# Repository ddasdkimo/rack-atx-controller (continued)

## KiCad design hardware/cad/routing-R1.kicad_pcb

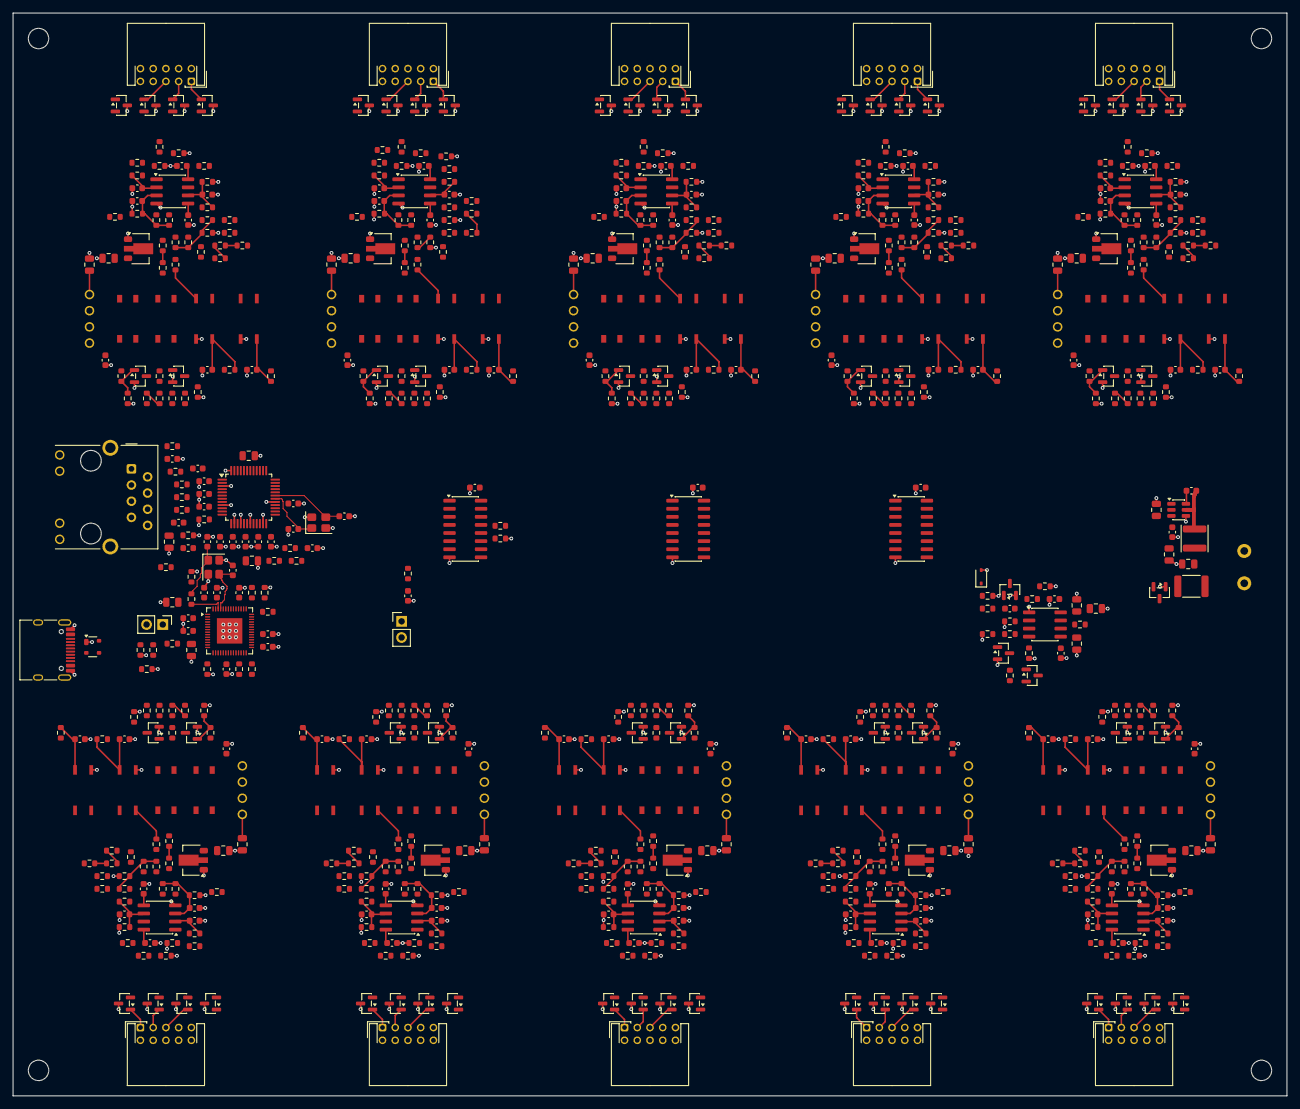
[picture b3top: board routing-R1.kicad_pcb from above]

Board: 2 copper layers, 200.0 x 170.0 mm, 698 parts (0 on the bottom side), 455 nets.

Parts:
C1, C14, C15, C27, C29, C43, C44, C45, C47, C48, C57, C58, C67, C68, C77, C78, C87, C88, C97, C98, C107, C108, C117, C118, C127, C128, C137, C138: 10u; C_0805_2012Metric
C2, C3, C6, C8, C9, C10, C11, C12, C13, C21, C22, C23, C24, C25, C26, C28, C37, C38, C39, C40, C42, C49, C59, C69, C79, C89, C99, C109, C119, C129, C139: 100n; C_0603_1608Metric
C4, C5: 22u; C_0805_2012Metric
C7, C16, C30: 1u; C_0603_1608Metric
C17, C18, C31, C32: 20p; C_0603_1608Metric
C19, C46, C56, C66, C76, C86, C96, C106, C116, C126, C136: 4.7u; C_0603_1608Metric
C20, C33, C41: 10n; C_0603_1608Metric
C34, C35: 6.8n; C_0603_1608Metric
C36: 22n; C_0805_2012Metric
C50, C51, C52, C53, C54, C55, C60, C61, C62, C63, C64, C65, C70, C71, C72, C73, C74, C75, C80, C81, C82, C83, C84, C85, C90, C91, C92, C93, C94, C95, C100, C101, C102, C103, C104, C105, C110, C111, C112, C113, C114, C115, C120, C121, C122, C123, C124, C125, C130, C131, C132, C133, C134, C135, C140, C141, C142, C143, C144, C145: 1n; C_0603_1608Metric
D1: PRTR5V0U2X,215; SOT-143
D2: 1N4148WS; D_SOD-323
D3, D4, D5, D6, D7, D8, D9, D10, D11, D12, D13, D14, D15, D16, D17, D18, D19, D20, D21, D22, D23, D24, D25, D26, D27, D28, D29, D30, D31, D32, D33, D34, D35, D36, D37, D38, D39, D40, D41, D42: PESD5V0S2BT; SOT-23
F1: MF-MSMF150/24X-2 1.5A; Fuse_1812_4532Metric
J01, J02, J03, J04, J05, J06, J07, J08, J09, J10: S10B-PHDSS(LF)(SN); JST_PHD_S10B-PHDSS_2x05_P2.00mm_Horizontal
J101: WJ500V-5.08-2P; WJ500V_5.08_2P
J102, J103: PZ254V-11-02P; PinHeader_1x02_P2.54mm_Vertical
J104: TYPE-C-31-M-12; USB_C_Receptacle_HRO_TYPE-C-31-M-12
J105: HR911105A; RJ45_Hanrun_HR911105A_Horizontal
L1: 4.7uH FNR4018S4R7MT; L_Changjiang_FNR4018S
L2: 120R@100MHz GZ1608D121TF; L_0603_1608Metric
MH1, MH2, MH3, MH4: MountingHole_3.2mm_M3
Q1, Q4: AO3401A; SOT-23
Q2, Q3, Q5, Q6, Q7, Q8, Q9, Q10, Q11, Q12, Q13, Q14, Q15, Q16, Q17, Q18, Q19, Q20, Q21, Q22, Q23, Q24: MMBT3904; SOT-23
R1, R2, R3, R4, R15, R16, R17, R25, R29, R30, R31, R33, R35, R36, R37, R47, R49, R55, R58, R60, R62, R68, R71, R72, R82, R84, R90, R93, R95, R97, R103, R106, R107, R117, R119, R125, R128, R130, R132, R138, R141, R142, R152, R154, R160, R163, R165, R167, R173, R176, R177, R187, R189, R195, R198, R200, R202, R208, R211, R212, R222, R224, R230, R233, R235, R237, R243, R246, R247, R257, R259, R265, R268, R270, R272, R278, R281, R282, R292, R294, R300, R303, R305, R307, R313, R316, R317, R327, R329, R335, R338, R340, R342, R348, R351, R352, R362, R364, R370, R373, R375, R377, R383, R386: 10k 1%; R_0603_1608Metric
R5, R24: 0 1%; R_0603_1608Metric
R6, R7: 47 1%; R_0603_1608Metric
R8, R9: 5.1k 1%; R_0603_1608Metric
R10, R11: 33 1%; R_0603_1608Metric
R12, R13, R26, R27, R28, R34, R39, R43, R46, R48, R59, R61, R74, R78, R81, R83, R94, R96, R109, R113, R116, R118, R129, R131, R144, R148, R151, R153, R164, R166, R179, R183, R186, R188, R199, R201, R214, R218, R221, R223, R234, R236, R249, R253, R256, R258, R269, R271, R284, R288, R291, R293, R304, R306, R319, R323, R326, R328, R339, R341, R354, R358, R361, R363, R374, R376: 100k 1%; R_0603_1608Metric
R14: 12.4k 1%; R_0603_1608Metric
R18, R19, R20, R21: 49.9 1%; R_0603_1608Metric
R22, R23, R56, R57, R69, R70, R91, R92, R104, R105, R126, R127, R139, R140, R161, R162, R174, R175, R196, R197, R209, R210, R231, R232, R244, R245, R266, R267, R279, R280, R301, R302, R314, R315, R336, R337, R349, R350, R371, R372, R384, R385: 330 1%; R_0603_1608Metric
R32, R51, R52, R53, R54, R64, R65, R66, R67, R86, R87, R88, R89, R99, R100, R101, R102, R121, R122, R123, R124, R134, R135, R136, R137, R156, R157, R158, R159, R169, R170, R171, R172, R191, R192, R193, R194, R204, R205, R206, R207, R226, R227, R228, R229, R239, R240, R241, R242, R261, R262, R263, R264, R274, R275, R276, R277, R296, R297, R298, R299, R309, R310, R311, R312, R331, R332, R333, R334, R344, R345, R346, R347, R366, R367, R368, R369, R379, R380, R381, R382: 510k 1%; R_0603_1608Metric
R38, R42, R73, R77, R108, R112, R143, R147, R178, R182, R213, R217, R248, R252, R283, R287, R318, R322, R353, R357: 1.5k 1%; R_0603_1608Metric
R40, R41, R44, R45, R75, R76, R79, R80, R110, R111, R114, R115, R145, R146, R149, R150, R180, R181, R184, R185, R215, R216, R219, R220, R250, R251, R254, R255, R285, R286, R289, R290, R320, R321, R324, R325, R355, R356, R359, R360: 220 1%; R_0603_1608Metric
R50, R63, R85, R98, R120, R133, R155, R168, R190, R203, R225, R238, R260, R273, R295, R308, R330, R343, R365, R378: 390k 1%; R_0603_1608Metric
U1: AP63203WU-7; TSOT-23-6
U2: ESP32-S3FN8; QFN-56-1EP_7x7mm_P0.4mm_EP4x4mm
U3: W5500; LQFP-48_7x7mm_P0.5mm
U4, U5, U6: 74HC595D,118; SOIC-16_3.9x9.9mm_P1.27mm
U7: TLC555CDR; SOIC-8_3.9x4.9mm_P1.27mm
U8, U15, U22, U29, U36, U43, U50, U57, U64, U71: B0505S-1WR3L; HENIPER_B0505S_1WR3L
U9, U16, U23, U30, U37, U44, U51, U58, U65, U72: HT7533-1; SOT-89-3
U10, U11, U17, U18, U24, U25, U31, U32, U38, U39, U45, U46, U52, U53, U59, U60, U66, U67, U73, U74: TLP3122A(TPL,E; TLP3122A_11-4M1S
U12, U13, U19, U20, U26, U27, U33, U34, U40, U41, U47, U48, U54, U55, U61, U62, U68, U69, U75, U76: EL357N(B)(TA)-G; EL357N_SOP4
U14, U21, U28, U35, U42, U49, U56, U63, U70, U77: LM393DR; SOIC-8_3.9x4.9mm_P1.27mm
Y1: 40MHz CL12pF; Crystal_SMD_3225-4Pin_3.2x2.5mm
Y2: 25MHz CL12pF; Crystal_SMD_3225-4Pin_3.2x2.5mm

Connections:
3V3: C4.1, C5.1, C8.1, C9.1, C10.1, C11.1, C12.1, C13.1, C14.1, C15.1, C28.1, C29.1, C37.1, C38.1, C39.1, L1.2, L2.1, R1.1, R2.1, R15.1, R16.1, R17.1, R22.1, R23.1, R25.1, R58.1, R71.1, R93.1, R106.1, R128.1, R141.1, R163.1, R176.1, R198.1, R211.1, R233.1, R246.1, R268.1, R281.1, R303.1, R316.1, R338.1, R351.1, R373.1, R386.1, U1.1, U2.2, U2.3, U2.20, U2.46, U2.55, U2.56, U3.28, U3.43, U3.44, U3.45, U4.16, U5.16, U6.16
3V3_ETH_A: C21.1, C22.1, C23.1, C24.1, C25.1, C26.1, C27.1, L2.2, R18.2, R19.2, U3.4, U3.8, U3.11, U3.15, U3.17, U3.21
5V: C1.1, C2.1, C42.1, C46.1, C56.1, C66.1, C76.1, C86.1, C96.1, C106.1, C116.1, C126.1, C136.1, Q1.2, Q4.2, R31.1, R32.1, R35.2, U1.2, U1.3, U7.8, U8.2, U15.2, U22.2, U29.2, U36.2, U43.2, U50.2, U57.2, U64.2, U71.2
5V_FUSED: F1.2, Q1.3
5V_JACK: F1.1, J101.1
BOOT_N: J103.1, R2.2, U2.5
BUCK_BST: C3.1, U1.6
BUCK_SW: C3.2, L1.1, U1.5
CHASSIS: J105.SH, R24.1
CTRL_H01_PWR_A: R41.2, U10.1
CTRL_H01_PWR_B: Q5.1, R38.2, R39.1
CTRL_H01_PWR_K: Q5.3, U10.3
CTRL_H01_PWR_R: R40.2, R41.1
CTRL_H01_RST_A: R45.2, U11.1
CTRL_H01_RST_B: Q6.1, R42.2, R43.1
CTRL_H01_RST_K: Q6.3, U11.3
CTRL_H01_RST_R: R44.2, R45.1
CTRL_H02_PWR_A: R76.2, U17.1
CTRL_H02_PWR_B: Q7.1, R73.2, R74.1
CTRL_H02_PWR_K: Q7.3, U17.3
CTRL_H02_PWR_R: R75.2, R76.1
CTRL_H02_RST_A: R80.2, U18.1
CTRL_H02_RST_B: Q8.1, R77.2, R78.1
CTRL_H02_RST_K: Q8.3, U18.3
CTRL_H02_RST_R: R79.2, R80.1
CTRL_H03_PWR_A: R111.2, U24.1
CTRL_H03_PWR_B: Q9.1, R108.2, R109.1
CTRL_H03_PWR_K: Q9.3, U24.3
CTRL_H03_PWR_R: R110.2, R111.1
CTRL_H03_RST_A: R115.2, U25.1
CTRL_H03_RST_B: Q10.1, R112.2, R113.1
CTRL_H03_RST_K: Q10.3, U25.3
CTRL_H03_RST_R: R114.2, R115.1
CTRL_H04_PWR_A: R146.2, U31.1
CTRL_H04_PWR_B: Q11.1, R143.2, R144.1
CTRL_H04_PWR_K: Q11.3, U31.3
CTRL_H04_PWR_R: R145.2, R146.1
CTRL_H04_RST_A: R150.2, U32.1
CTRL_H04_RST_B: Q12.1, R147.2, R148.1
CTRL_H04_RST_K: Q12.3, U32.3
CTRL_H04_RST_R: R149.2, R150.1
CTRL_H05_PWR_A: R181.2, U38.1
CTRL_H05_PWR_B: Q13.1, R178.2, R179.1
CTRL_H05_PWR_K: Q13.3, U38.3
CTRL_H05_PWR_R: R180.2, R181.1
CTRL_H05_RST_A: R185.2, U39.1
CTRL_H05_RST_B: Q14.1, R182.2, R183.1
CTRL_H05_RST_K: Q14.3, U39.3
CTRL_H05_RST_R: R184.2, R185.1
CTRL_H06_PWR_A: R216.2, U45.1
CTRL_H06_PWR_B: Q15.1, R213.2, R214.1
CTRL_H06_PWR_K: Q15.3, U45.3
CTRL_H06_PWR_R: R215.2, R216.1
CTRL_H06_RST_A: R220.2, U46.1
CTRL_H06_RST_B: Q16.1, R217.2, R218.1
CTRL_H06_RST_K: Q16.3, U46.3
CTRL_H06_RST_R: R219.2, R220.1
CTRL_H07_PWR_A: R251.2, U52.1
CTRL_H07_PWR_B: Q17.1, R248.2, R249.1
CTRL_H07_PWR_K: Q17.3, U52.3
CTRL_H07_PWR_R: R250.2, R251.1
CTRL_H07_RST_A: R255.2, U53.1
CTRL_H07_RST_B: Q18.1, R252.2, R253.1
CTRL_H07_RST_K: Q18.3, U53.3
CTRL_H07_RST_R: R254.2, R255.1
CTRL_H08_PWR_A: R286.2, U59.1
CTRL_H08_PWR_B: Q19.1, R283.2, R284.1
CTRL_H08_PWR_K: Q19.3, U59.3
CTRL_H08_PWR_R: R285.2, R286.1
CTRL_H08_RST_A: R290.2, U60.1
CTRL_H08_RST_B: Q20.1, R287.2, R288.1
CTRL_H08_RST_K: Q20.3, U60.3
CTRL_H08_RST_R: R289.2, R290.1
CTRL_H09_PWR_A: R321.2, U66.1
CTRL_H09_PWR_B: Q21.1, R318.2, R319.1
CTRL_H09_PWR_K: Q21.3, U66.3
CTRL_H09_PWR_R: R320.2, R321.1
CTRL_H09_RST_A: R325.2, U67.1
CTRL_H09_RST_B: Q22.1, R322.2, R323.1
CTRL_H09_RST_K: Q22.3, U67.3
CTRL_H09_RST_R: R324.2, R325.1
CTRL_H10_PWR_A: R356.2, U73.1
CTRL_H10_PWR_B: Q23.1, R353.2, R354.1
CTRL_H10_PWR_K: Q23.3, U73.3
CTRL_H10_PWR_R: R355.2, R356.1
CTRL_H10_RST_A: R360.2, U74.1
CTRL_H10_RST_B: Q24.1, R357.2, R358.1
CTRL_H10_RST_K: Q24.3, U74.3
CTRL_H10_RST_R: R359.2, R360.1
DRV_01: R38.1, U4.15
DRV_02: R42.1, U4.1
DRV_03: R73.1, U4.2
DRV_04: R77.1, U4.3
DRV_05: R108.1, U4.4
DRV_06: R112.1, U4.5
DRV_07: R143.1, U4.6
DRV_08: R147.1, U4.7
DRV_09: R178.1, U5.15
DRV_10: R182.1, U5.1
DRV_11: R213.1, U5.2
DRV_12: R217.1, U5.3
DRV_13: R248.1, U5.4
DRV_14: R252.1, U5.5
DRV_15: R283.1, U5.6
DRV_16: R287.1, U5.7
DRV_17: R318.1, U6.15
DRV_18: R322.1, U6.1
DRV_19: R353.1, U6.2
DRV_20: R357.1, U6.3
EN: C16.1, J102.1, R1.2, U2.4, U4.10, U5.10, U6.10
ETH_1V2: C20.1, U3.22
ETH_ACT_N: J105.11, U3.27
ETH_CS_N: R15.2, U2.48, U3.32
ETH_EXRES: R14.1, U3.10
ETH_INT_N: R16.2, U2.37, U3.36
ETH_LINK_N: J105.10, U3.25
ETH_RST_N: C30.1, R17.2, U2.36, U3.37
ETH_RXN: C35.1, R21.1, U3.5
ETH_RXP: C34.1, R20.1, U3.6
ETH_RX_TERM: C33.1, J105.5, R20.2, R21.2
ETH_TOCAP: C19.1, U3.20
ETH_TXN: J105.2, R19.1, U3.1
ETH_TXP: J105.1, R18.1, U3.2
ETH_XI: C31.1, U3.30, Y2.1
ETH_XO: C32.1, U3.31, Y2.3
GATE_BASE: Q3.1, R33.2, R34.1
GND_CTRL: C1.2, C2.2, C4.2, C5.2, C6.2, C7.2, C8.2, C9.2, C10.2, C11.2, C12.2, C13.2, C14.2, C15.2, C16.2, C17.2, C18.2, C19.2, C20.2, C21.2, C22.2, C23.2, C24.2, C25.2, C26.2, C27.2, C28.2, C29.2, C30.2, C31.2, C32.2, C33.2, C36.2, C37.2, C38.2, C39.2, C41.2, C42.2, C43.2, C44.2, C45.2, C46.2, C52.2, C55.2, C56.2, C62.2, C65.2, C66.2, C72.2, C75.2, C76.2, C82.2, C85.2, C86.2, C92.2, C95.2, C96.2, C102.2, C105.2, C106.2, C112.2, C115.2, C116.2, C122.2, C125.2, C126.2, C132.2, C135.2, C136.2, C142.2, C145.2, D1.1, D2.2, J101.2, J102.2, J103.2, J104.A1, J104.A12, J104.B1, J104.B12, J104.SH, J105.8, Q1.1, Q2.2, Q3.2, Q5.2, Q6.2, Q7.2, Q8.2, Q9.2, Q10.2, Q11.2, Q12.2, Q13.2, Q14.2, Q15.2, Q16.2, Q17.2, Q18.2, Q19.2, Q20.2, Q21.2, Q22.2, Q23.2, Q24.2, R3.2, R4.2, R8.2, R9.2, R13.2, R14.2, R24.2, R26.2, R27.2, R28.2, R30.2, R34.2, R36.2, R39.2, R43.2, R74.2, R78.2, R109.2, R113.2, R144.2, R148.2, R179.2, R183.2, R214.2, R218.2, R249.2, R253.2, R284.2, R288.2, R319.2, R323.2, R354.2, R358.2, U1.4, U2.57, U3.3, U3.9, U3.14, U3.16, U3.19, U3.23, U3.29, U3.48, U4.8, U5.8, U6.8, U7.1, U8.1, U12.3, U13.3, U15.1, U19.3, U20.3, U22.1, U26.3, U27.3, U29.1, U33.3, U34.3, U36.1, U40.3, U41.3, U43.1, U47.3, U48.3, U50.1, U54.3, U55.3, U57.1, U61.3, U62.3, U64.1, U68.3, U69.3, U71.1, U75.3, U76.3, Y1.2, Y1.4, Y2.2, Y2.4
H01_3V3: C48.1, C49.1, R37.1, R50.1, R55.1, R56.1, R63.1, R68.1, R69.1, U9.3, U14.8
H01_GND: C47.2, C48.2, C49.2, C50.2, C51.2, C53.2, C54.2, D3.3, D4.3, D5.3, D6.3, J01.9, R37.2, R47.2, R49.2, R60.2, R62.2, U8.3, U9.1, U14.4
H01_HDD_CMP: R64.1, R68.2, U13.2, U14.7
H01_HDD_FB1: R64.2, R65.1
H01_HDD_FB2: R65.2, R66.1
H01_HDD_FB3: R66.2, R67.1
H01_HDD_M: D6.2, J01.8, R61.1
H01_HDD_N: C55.1, R71.2, U2.10, U13.4
H01_HDD_OA: R70.2, U13.1
H01_HDD_OR: R69.2, R70.1
H01_HDD_P: D6.1, J01.7, R59.1
H01_HDD_SMINUS: C54.1, R61.2, R62.1, R63.2, R67.2, U14.5
H01_HDD_SPLUS: C53.1, R59.2, R60.1, U14.6
H01_PLED_CMP: R51.1, R55.2, U12.2, U14.1
H01_PLED_FB1: R51.2, R52.1
H01_PLED_FB2: R52.2, R53.1
H01_PLED_FB3: R53.2, R54.1
H01_PLED_M: D5.2, J01.6, R48.1
H01_PLED_N: C52.1, R58.2, U2.9, U12.4
H01_PLED_OA: R57.2, U12.1
H01_PLED_OR: R56.2, R57.1
H01_PLED_P: D5.1, J01.5, R46.1
H01_PLED_SMINUS: C51.1, R48.2, R49.1, R50.2, R54.2, U14.3
H01_PLED_SPLUS: C50.1, R46.2, R47.1, U14.2
H01_PWR_A: D3.1, J01.1, U10.4
H01_PWR_B: D3.2, J01.2, U10.6
H01_RAW5: C47.1, U8.4, U9.2
H01_RST_A: D4.1, J01.3, U11.4
H01_RST_B: D4.2, J01.4, U11.6
H02_3V3: C58.1, C59.1, R72.1, R85.1, R90.1, R91.1, R98.1, R103.1, R104.1, U16.3, U21.8
H02_GND: C57.2, C58.2, C59.2, C60.2, C61.2, C63.2, C64.2, D7.3, D8.3, D9.3, D10.3, J02.9, R72.2, R82.2, R84.2, R95.2, R97.2, U15.3, U16.1, U21.4
H02_HDD_CMP: R99.1, R103.2, U20.2, U21.7
H02_HDD_FB1: R99.2, R100.1
H02_HDD_FB2: R100.2, R101.1
H02_HDD_FB3: R101.2, R102.1
H02_HDD_M: D10.2, J02.8, R96.1
H02_HDD_N: C65.1, R106.2, U2.12, U20.4
H02_HDD_OA: R105.2, U20.1
H02_HDD_OR: R104.2, R105.1
H02_HDD_P: D10.1, J02.7, R94.1
H02_HDD_SMINUS: C64.1, R96.2, R97.1, R98.2, R102.2, U21.5
H02_HDD_SPLUS: C63.1, R94.2, R95.1, U21.6
H02_PLED_CMP: R86.1, R90.2, U19.2, U21.1
H02_PLED_FB1: R86.2, R87.1
H02_PLED_FB2: R87.2, R88.1
H02_PLED_FB3: R88.2, R89.1
H02_PLED_M: D9.2, J02.6, R83.1
H02_PLED_N: C62.1, R93.2, U2.11, U19.4
H02_PLED_OA: R92.2, U19.1
H02_PLED_OR: R91.2, R92.1
H02_PLED_P: D9.1, J02.5, R81.1
H02_PLED_SMINUS: C61.1, R83.2, R84.1, R85.2, R89.2, U21.3
H02_PLED_SPLUS: C60.1, R81.2, R82.1, U21.2
H02_PWR_A: D7.1, J02.1, U17.4
H02_PWR_B: D7.2, J02.2, U17.6
H02_RAW5: C57.1, U15.4, U16.2
H02_RST_A: D8.1, J02.3, U18.4
H02_RST_B: D8.2, J02.4, U18.6
H03_3V3: C68.1, C69.1, R107.1, R120.1, R125.1, R126.1, R133.1, R138.1, R139.1, U23.3, U28.8
H03_GND: C67.2, C68.2, C69.2, C70.2, C71.2, C73.2, C74.2, D11.3, D12.3, D13.3, D14.3, J03.9, R107.2, R117.2, R119.2, R130.2, R132.2, U22.3, U23.1, U28.4
H03_HDD_CMP: R134.1, R138.2, U27.2, U28.7
H03_HDD_FB1: R134.2, R135.1
H03_HDD_FB2: R135.2, R136.1
H03_HDD_FB3: R136.2, R137.1
H03_HDD_M: D14.2, J03.8, R131.1
H03_HDD_N: C75.1, R141.2, U2.14, U27.4
H03_HDD_OA: R140.2, U27.1
H03_HDD_OR: R139.2, R140.1
H03_HDD_P: D14.1, J03.7, R129.1
H03_HDD_SMINUS: C74.1, R131.2, R132.1, R133.2, R137.2, U28.5
H03_HDD_SPLUS: C73.1, R129.2, R130.1, U28.6
H03_PLED_CMP: R121.1, R125.2, U26.2, U28.1
H03_PLED_FB1: R121.2, R122.1
H03_PLED_FB2: R122.2, R123.1
H03_PLED_FB3: R123.2, R124.1
H03_PLED_M: D13.2, J03.6, R118.1
H03_PLED_N: C72.1, R128.2, U2.13, U26.4
H03_PLED_OA: R127.2, U26.1
H03_PLED_OR: R126.2, R127.1
H03_PLED_P: D13.1, J03.5, R116.1
H03_PLED_SMINUS: C71.1, R118.2, R119.1, R120.2, R124.2, U28.3
H03_PLED_SPLUS: C70.1, R116.2, R117.1, U28.2
H03_PWR_A: D11.1, J03.1, U24.4
H03_PWR_B: D11.2, J03.2, U24.6
H03_RAW5: C67.1, U22.4, U23.2
H03_RST_A: D12.1, J03.3, U25.4
H03_RST_B: D12.2, J03.4, U25.6
H04_3V3: C78.1, C79.1, R142.1, R155.1, R160.1, R161.1, R168.1, R173.1, R174.1, U30.3, U35.8
H04_GND: C77.2, C78.2, C79.2, C80.2, C81.2, C83.2, C84.2, D15.3, D16.3, D17.3, D18.3, J04.9, R142.2, R152.2, R154.2, R165.2, R167.2, U29.3, U30.1, U35.4
H04_HDD_CMP: R169.1, R173.2, U34.2, U35.7
H04_HDD_FB1: R169.2, R170.1
H04_HDD_FB2: R170.2, R171.1
H04_HDD_FB3: R171.2, R172.1
H04_HDD_M: D18.2, J04.8, R166.1
H04_HDD_N: C85.1, R176.2, U2.16, U34.4
H04_HDD_OA: R175.2, U34.1
H04_HDD_OR: R174.2, R175.1
H04_HDD_P: D18.1, J04.7, R164.1
H04_HDD_SMINUS: C84.1, R166.2, R167.1, R168.2, R172.2, U35.5
H04_HDD_SPLUS: C83.1, R164.2, R165.1, U35.6
H04_PLED_CMP: R156.1, R160.2, U33.2, U35.1
H04_PLED_FB1: R156.2, R157.1
H04_PLED_FB2: R157.2, R158.1
H04_PLED_FB3: R158.2, R159.1
H04_PLED_M: D17.2, J04.6, R153.1
H04_PLED_N: C82.1, R163.2, U2.15, U33.4
H04_PLED_OA: R162.2, U33.1
H04_PLED_OR: R161.2, R162.1
H04_PLED_P: D17.1, J04.5, R151.1
H04_PLED_SMINUS: C81.1, R153.2, R154.1, R155.2, R159.2, U35.3
H04_PLED_SPLUS: C80.1, R151.2, R152.1, U35.2
H04_PWR_A: D15.1, J04.1, U31.4
H04_PWR_B: D15.2, J04.2, U31.6
H04_RAW5: C77.1, U29.4, U30.2
H04_RST_A: D16.1, J04.3, U32.4
H04_RST_B: D16.2, J04.4, U32.6
H05_3V3: C88.1, C89.1, R177.1, R190.1, R195.1, R196.1, R203.1, R208.1, R209.1, U37.3, U42.8
H05_GND: C87.2, C88.2, C89.2, C90.2, C91.2, C93.2, C94.2, D19.3, D20.3, D21.3, D22.3, J05.9, R177.2, R187.2, R189.2, R200.2, R202.2, U36.3, U37.1, U42.4
H05_HDD_CMP: R204.1, R208.2, U41.2, U42.7
H05_HDD_FB1: R204.2, R205.1
H05_HDD_FB2: R205.2, R206.1
H05_HDD_FB3: R206.2, R207.1
H05_HDD_M: D22.2, J05.8, R201.1
H05_HDD_N: C95.1, R211.2, U2.18, U41.4
H05_HDD_OA: R210.2, U41.1
H05_HDD_OR: R209.2, R210.1
H05_HDD_P: D22.1, J05.7, R199.1
H05_HDD_SMINUS: C94.1, R201.2, R202.1, R203.2, R207.2, U42.5
H05_HDD_SPLUS: C93.1, R199.2, R200.1, U42.6
H05_PLED_CMP: R191.1, R195.2, U40.2, U42.1
H05_PLED_FB1: R191.2, R192.1
H05_PLED_FB2: R192.2, R193.1
H05_PLED_FB3: R193.2, R194.1
H05_PLED_M: D21.2, J05.6, R188.1
H05_PLED_N: C92.1, R198.2, U2.17, U40.4
H05_PLED_OA: R197.2, U40.1
H05_PLED_OR: R196.2, R197.1
H05_PLED_P: D21.1, J05.5, R186.1
H05_PLED_SMINUS: C91.1, R188.2, R189.1, R190.2, R194.2, U42.3
H05_PLED_SPLUS: C90.1, R186.2, R187.1, U42.2
H05_PWR_A: D19.1, J05.1, U38.4
H05_PWR_B: D19.2, J05.2, U38.6
H05_RAW5: C87.1, U36.4, U37.2
H05_RST_A: D20.1, J05.3, U39.4
H05_RST_B: D20.2, J05.4, U39.6
H06_3V3: C98.1, C99.1, R212.1, R225.1, R230.1, R231.1, R238.1, R243.1, R244.1, U44.3, U49.8
H06_GND: C97.2, C98.2, C99.2, C100.2, C101.2, C103.2, C104.2, D23.3, D24.3, D25.3, D26.3, J06.9, R212.2, R222.2, R224.2, R235.2, R237.2, U43.3, U44.1, U49.4
H06_HDD_CMP: R239.1, R243.2, U48.2, U49.7
H06_HDD_FB1: R239.2, R240.1
H06_HDD_FB2: R240.2, R241.1
H06_HDD_FB3: R241.2, R242.1
H06_HDD_M: D26.2, J06.8, R236.1
H06_HDD_N: C105.1, R246.2, U2.21, U48.4
H06_HDD_OA: R245.2, U48.1
H06_HDD_OR: R244.2, R245.1
H06_HDD_P: D26.1, J06.7, R234.1
H06_HDD_SMINUS: C104.1, R236.2, R237.1, R238.2, R242.2, U49.5
H06_HDD_SPLUS: C103.1, R234.2, R235.1, U49.6
H06_PLED_CMP: R226.1, R230.2, U47.2, U49.1
H06_PLED_FB1: R226.2, R227.1
H06_PLED_FB2: R227.2, R228.1
H06_PLED_FB3: R228.2, R229.1
H06_PLED_M: D25.2, J06.6, R223.1
H06_PLED_N: C102.1, R233.2, U2.19, U47.4
H06_PLED_OA: R232.2, U47.1
H06_PLED_OR: R231.2, R232.1
H06_PLED_P: D25.1, J06.5, R221.1
H06_PLED_SMINUS: C101.1, R223.2, R224.1, R225.2, R229.2, U49.3
H06_PLED_SPLUS: C100.1, R221.2, R222.1, U49.2
H06_PWR_A: D23.1, J06.1, U45.4
H06_PWR_B: D23.2, J06.2, U45.6
H06_RAW5: C97.1, U43.4, U44.2
H06_RST_A: D24.1, J06.3, U46.4
H06_RST_B: D24.2, J06.4, U46.6
H07_3V3: C108.1, C109.1, R247.1, R260.1, R265.1, R266.1, R273.1, R278.1, R279.1, U51.3, U56.8
H07_GND: C107.2, C108.2, C109.2, C110.2, C111.2, C113.2, C114.2, D27.3, D28.3, D29.3, D30.3, J07.9, R247.2, R257.2, R259.2, R270.2, R272.2, U50.3, U51.1, U56.4
H07_HDD_CMP: R274.1, R278.2, U55.2, U56.7
H07_HDD_FB1: R274.2, R275.1
H07_HDD_FB2: R275.2, R276.1
H07_HDD_FB3: R276.2, R277.1
H07_HDD_M: D30.2, J07.8, R271.1
H07_HDD_N: C115.1, R281.2, U2.23, U55.4
H07_HDD_OA: R280.2, U55.1
H07_HDD_OR: R279.2, R280.1
H07_HDD_P: D30.1, J07.7, R269.1
H07_HDD_SMINUS: C114.1, R271.2, R272.1, R273.2, R277.2, U56.5
H07_HDD_SPLUS: C113.1, R269.2, R270.1, U56.6
H07_PLED_CMP: R261.1, R265.2, U54.2, U56.1
H07_PLED_FB1: R261.2, R262.1
H07_PLED_FB2: R262.2, R263.1
H07_PLED_FB3: R263.2, R264.1
H07_PLED_M: D29.2, J07.6, R258.1
H07_PLED_N: C112.1, R268.2, U2.22, U54.4
H07_PLED_OA: R267.2, U54.1
H07_PLED_OR: R266.2, R267.1
H07_PLED_P: D29.1, J07.5, R256.1
H07_PLED_SMINUS: C111.1, R258.2, R259.1, R260.2, R264.2, U56.3
H07_PLED_SPLUS: C110.1, R256.2, R257.1, U56.2
H07_PWR_A: D27.1, J07.1, U52.4
H07_PWR_B: D27.2, J07.2, U52.6
H07_RAW5: C107.1, U50.4, U51.2
H07_RST_A: D28.1, J07.3, U53.4
H07_RST_B: D28.2, J07.4, U53.6
H08_3V3: C118.1, C119.1, R282.1, R295.1, R300.1, R301.1, R308.1, R313.1, R314.1, U58.3, U63.8
H08_GND: C117.2, C118.2, C119.2, C120.2, C121.2, C123.2, C124.2, D31.3, D32.3, D33.3, D34.3, J08.9, R282.2, R292.2, R294.2, R305.2, R307.2, U57.3, U58.1, U63.4
H08_HDD_CMP: R309.1, R313.2, U62.2, U63.7
H08_HDD_FB1: R309.2, R310.1
H08_HDD_FB2: R310.2, R311.1
H08_HDD_FB3: R311.2, R312.1
H08_HDD_M: D34.2, J08.8, R306.1
H08_HDD_N: C125.1, R316.2, U2.27, U62.4
H08_HDD_OA: R315.2, U62.1
H08_HDD_OR: R314.2, R315.1
H08_HDD_P: D34.1, J08.7, R304.1
H08_HDD_SMINUS: C124.1, R306.2, R307.1, R308.2, R312.2, U63.5
H08_HDD_SPLUS: C123.1, R304.2, R305.1, U63.6
H08_PLED_CMP: R296.1, R300.2, U61.2, U63.1
H08_PLED_FB1: R296.2, R297.1
H08_PLED_FB2: R297.2, R298.1
H08_PLED_FB3: R298.2, R299.1
H08_PLED_M: D33.2, J08.6, R293.1
H08_PLED_N: C122.1, R303.2, U2.24, U61.4
H08_PLED_OA: R302.2, U61.1
H08_PLED_OR: R301.2, R302.1
H08_PLED_P: D33.1, J08.5, R291.1
H08_PLED_SMINUS: C121.1, R293.2, R294.1, R295.2, R299.2, U63.3
H08_PLED_SPLUS: C120.1, R291.2, R292.1, U63.2
H08_PWR_A: D31.1, J08.1, U59.4
H08_PWR_B: D31.2, J08.2, U59.6
H08_RAW5: C117.1, U57.4, U58.2
H08_RST_A: D32.1, J08.3, U60.4
H08_RST_B: D32.2, J08.4, U60.6
H09_3V3: C128.1, C129.1, R317.1, R330.1, R335.1, R336.1, R343.1, R348.1, R349.1, U65.3, U70.8
H09_GND: C127.2, C128.2, C129.2, C130.2, C131.2, C133.2, C134.2, D35.3, D36.3, D37.3, D38.3, J09.9, R317.2, R327.2, R329.2, R340.2, R342.2, U64.3, U65.1, U70.4
H09_HDD_CMP: R344.1, R348.2, U69.2, U70.7
H09_HDD_FB1: R344.2, R345.1
H09_HDD_FB2: R345.2, R346.1
H09_HDD_FB3: R346.2, R347.1
H09_HDD_M: D38.2, J09.8, R341.1
H09_HDD_N: C135.1, R351.2, U2.41, U69.4
H09_HDD_OA: R350.2, U69.1
H09_HDD_OR: R349.2, R350.1
H09_HDD_P: D38.1, J09.7, R339.1
H09_HDD_SMINUS: C134.1, R341.2, R342.1, R343.2, R347.2, U70.5
H09_HDD_SPLUS: C133.1, R339.2, R340.1, U70.6
H09_PLED_CMP: R331.1, R335.2, U68.2, U70.1
H09_PLED_FB1: R331.2, R332.1
H09_PLED_FB2: R332.2, R333.1
H09_PLED_FB3: R333.2, R334.1
H09_PLED_M: D37.2, J09.6, R328.1
H09_PLED_N: C132.1, R338.2, U2.40, U68.4
H09_PLED_OA: R337.2, U68.1
H09_PLED_OR: R336.2, R337.1
H09_PLED_P: D37.1, J09.5, R326.1
H09_PLED_SMINUS: C131.1, R328.2, R329.1, R330.2, R334.2, U70.3
H09_PLED_SPLUS: C130.1, R326.2, R327.1, U70.2
H09_PWR_A: D35.1, J09.1, U66.4
H09_PWR_B: D35.2, J09.2, U66.6
H09_RAW5: C127.1, U64.4, U65.2
H09_RST_A: D36.1, J09.3, U67.4
H09_RST_B: D36.2, J09.4, U67.6
H10_3V3: C138.1, C139.1, R352.1, R365.1, R370.1, R371.1, R378.1, R383.1, R384.1, U72.3, U77.8
H10_GND: C137.2, C138.2, C139.2, C140.2, C141.2, C143.2, C144.2, D39.3, D40.3, D41.3, D42.3, J10.9, R352.2, R362.2, R364.2, R375.2, R377.2, U71.3, U72.1, U77.4
H10_HDD_CMP: R379.1, R383.2, U76.2, U77.7
H10_HDD_FB1: R379.2, R380.1
H10_HDD_FB2: R380.2, R381.1
H10_HDD_FB3: R381.2, R382.1
H10_HDD_M: D42.2, J10.8, R376.1
H10_HDD_N: C145.1, R386.2, U2.43, U76.4
H10_HDD_OA: R385.2, U76.1
H10_HDD_OR: R384.2, R385.1
H10_HDD_P: D42.1, J10.7, R374.1
H10_HDD_SMINUS: C144.1, R376.2, R377.1, R378.2, R382.2, U77.5
H10_HDD_SPLUS: C143.1, R374.2, R375.1, U77.6
H10_PLED_CMP: R366.1, R370.2, U75.2, U77.1
H10_PLED_FB1: R366.2, R367.1
H10_PLED_FB2: R367.2, R368.1
H10_PLED_FB3: R368.2, R369.1
H10_PLED_M: D41.2, J10.6, R363.1
H10_PLED_N: C142.1, R373.2, U2.42, U75.4
H10_PLED_OA: R372.2, U75.1
H10_PLED_OR: R371.2, R372.1
H10_PLED_P: D41.1, J10.5, R361.1
H10_PLED_SMINUS: C141.1, R363.2, R364.1, R365.2, R369.2, U77.3
H10_PLED_SPLUS: C140.1, R361.2, R362.1, U77.2
H10_PWR_A: D39.1, J10.1, U73.4
H10_PWR_B: D39.2, J10.2, U73.6
H10_RAW5: C137.1, U71.4, U72.2
H10_RST_A: D40.1, J10.3, U74.4
H10_RST_B: D40.2, J10.4, U74.6
MCU_XN: C18.1, U2.53, Y1.3
MCU_XP: R5.1, U2.54
MCU_XP_CR: C17.1, R5.2, Y1.1
OUT_LATCH: R26.1, U2.6, U4.12, U5.12, U6.12
OUT_OE_N: R25.2, U2.7, U4.13, U5.13, U6.13
PHOTO_5V: Q4.3, R36.1, R40.1, R44.1, R75.1, R79.1, R110.1, R114.1, R145.1, R149.1, R180.1, R184.1, R215.1, R219.1, R250.1, R254.1, R285.1, R289.1, R320.1, R324.1, R355.1, R359.1
PHOTO_GATE: Q3.3, Q4.1, R35.1
RJ_LED_G_A: J105.9, R22.2
RJ_LED_Y_A: J105.12, R23.2
RJ_RD_N: C35.2, J105.6
RJ_RD_P: C34.2, J105.3
RJ_TX_CT: C36.1, J105.4
SHIFT_1: U4.9, U5.14
SHIFT_2: U5.9, U6.14
SPI_MISO: U2.47, U3.34
SPI_MOSI: R7.2, U3.35, U4.14
SPI_MOSI_RAW: R7.1, U2.45
SPI_SCK: R6.2, U3.33, U4.11, U5.11, U6.11
SPI_SCK_RAW: R6.1, U2.44
STRAP45: R3.1, U2.51
STRAP46: R4.1, U2.52
TIMER_ARM: R27.1, U2.49, U7.4
TIMER_CTRL: C41.1, U7.5
TIMER_FIRE: C40.1, R28.1, U2.50
TIMER_OUT: R33.1, U7.3
TIMER_RC: C43.1, C44.1, C45.1, R32.2, U7.6, U7.7
TRIG_AC: C40.2, R29.1
TRIG_BASE: D2.1, Q2.1, R29.2, R30.1
TRIG_N: Q2.3, R31.2, U7.2
USB_CC1: J104.A5, R8.1
USB_CC2: J104.B5, R9.1
USB_DM: D1.2, J104.A7, J104.B7, R10.1
USB_DM_MCU: R10.2, U2.25
USB_DP: D1.3, J104.A6, J104.B6, R11.1
USB_DP_MCU: R11.2, U2.26
USB_VBUS: D1.4, J104.A4, J104.A9, J104.B4, J104.B9, R12.1
USB_VBUS_SENSE: R12.2, R13.1, U2.38
VDD_SPI: C6.1, C7.1, U2.29

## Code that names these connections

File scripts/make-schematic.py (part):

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part('cmp','C67470','LM393DR','Package_SO:SOIC-8_3.9x4.9mm_P1.27mm',pins('OUT1,IN1-,IN1+,GND,IN2+,IN2-,OUT2,VCC',{'1':'open_collector','7':'open_collector','2':'input','3':'input','5':'input','6':'input','4':'power_in','8':'power_in'}))
part('iso','C20622559','B0505S-1WR3L','Rack:HENIPER_B0505S-1WR3L',pins('GND_IN,VIN,GND_ISO,VOUT_ISO',{'1':'power_in','2':'power_in','3':'power_out','4':'power_out'}))
part('ldo','C14289','HT7533-1','Package_TO_SOT_SMD:SOT-89-3',pins('GND,VIN,VOUT',{'1':'power_in','2':'power_in','3':'power_out'}))
part('port','C161672','S10B-PHDSS(LF)(SN)','Connector_JST:JST_PHD_S10B-PHDSS_2x05_P2.00mm_Horizontal',pins('PWR_A,PWR_B,RST_A,RST_B,NC5,NC6,NC7,NC8,HOST_REF,NC10'))
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part('hc595','C5947','74HC595D,118','Package_SO:SOIC-16_3.9x9.9mm_P1.27mm',pins('QB,QC,QD,QE,QF,QG,QH,GND,QH_SER,MR_N,SHCP,STCP,OE_N,DS,QA,VCC',{**{str(i):'output' for i in [1,2,3,4,5,6,7,9,15]},**{str(i):'input' for i in [10,11,12,13,14]},'8':'power_in','16':'power_in'}))
part('timer','C7292','MC14541BDR2G','Package_SO:SOIC-14_3.9x8.7mm_P1.27mm',pins('RTC,CTC,RS,NC,AR,MR,GND,Q,QSEL,MODE,NC,A,B,VDD',{'1':'output','2':'output','3':'input','5':'input','6':'input','7':'power_in','8':'output','9':'input','10':'input','12':'input','13':'input','14':'power_in'}))
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add('barrel',['5V_JACK',G],ref='J101');add('fuse',['5V_JACK','5V_FUSED']);add('pmos',[G,V5,'5V_FUSED']);flag(G);flag('5V_JACK');flag('5V_FUSED');flag(V5);flag(V)
cap('10u',V5,G);cap('100n',V5,G)
add('buck',[V,V5,V5,G,'BUCK_SW','BUCK_BST']);cap('100n','BUCK_BST','BUCK_SW');add('ind',['BUCK_SW',V]);cap('22u',V,G);cap('22u',V,G)
page('processor','ESP32-S3FN8 / USB programming','Wired Ethernet only. Leave LNA_IN open and never initialize Wi-Fi/BLE.\nGPIO26..32 used by internal quad flash: do not route. GPIO45 pulled low selects 3.3 V flash.')
# GPIO numbers -> physical package pins
mapping={0:5,1:6,2:7,3:8,**{i:i+5 for i in range(4,15)},15:21,16:22,17:23,18:24,19:25,20:26,21:27,33:38,34:39,35:40,36:41,37:42,38:43,39:44,40:45,41:47,42:48,43:49,44:50,45:51,46:52,47:36,48:37}
mn={n:None for n,_,_ in mpins}
for n in ['2','3','20','46','55','56']:mn[n]=V
mn['57']=G;mn['4']='EN';mn['29']='VDD_SPI';mn['53']='MCU_XN';mn['54']='MCU_XP'
gpio={0:'BOOT_N',4:'TIMER_ARM',6:'OUT_OE_N',7:'OUT_LATCH',19:'USB_DM_MCU',20:'USB_DP_MCU',33:'USB_VBUS_SENSE',39:'SPI_SCK_RAW',40:'SPI_MOSI_RAW',41:'SPI_MISO',42:'ETH_CS_N',45:'STRAP45',46:'STRAP46',47:'ETH_RST_N',48:'ETH_INT_N'}
for g,n in gpio.items():mn[str(mapping[g])]=n
add('mcu',mn);cap('100n','VDD_SPI',G);cap('1u','VDD_SPI',G)
for _ in range(6):cap('100n',V,G)
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add('header2',['EN',G],ref='J102');add('header2',['BOOT_N',G],ref='J103')
add('xtal40',['MCU_XP_CR',G,'MCU_XN',G]);r('0','MCU_XP','MCU_XP_CR');cap('20p','MCU_XP_CR',G);cap('20p','MCU_XN',G)
r('47','SPI_SCK_RAW','SPI_SCK');r('47','SPI_MOSI_RAW','SPI_MOSI')
usb={n:G if n in ['A1','A12','B1','B12','SH'] else 'USB_VBUS' if n in ['A4','A9','B4','B9'] else 'USB_DP' if n in ['A6','B6'] else 'USB_DM' if n in ['A7','B7'] else 'USB_CC1' if n=='A5' else 'USB_CC2' if n=='B5' else None for n,_,_ in P['usb']['pins']}
add('usb',usb,ref='J104');add('usbesd',[G,'USB_DM','USB_DP','USB_VBUS']);r('5.1k','USB_CC1',G);r('5.1k','USB_CC2',G);r('33','USB_DM','USB_DM_MCU');r('33','USB_DP','USB_DP_MCU');r('100k','USB_VBUS','USB_VBUS_SENSE');r('100k','USB_VBUS_SENSE',G)
page('ethernet','W5500 / HR911105A Ethernet','WIZnet RJ45 reference topology. HR911105A pin numbering differs from J1B1211CCD.\n100-ohm differential MDI routing; crystal load caps need final frequency measurement.')
wn={str(i):None for i in range(1,49)}
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
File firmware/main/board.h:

// Rack ATX controller B.2 -- board definitions derived from hardware/circuit.json (revision B.2).
// Pin numbers are ESP32-S3 GPIO numbers. Verify against the released schematic before flashing.
#pragma once

#define FW_VERSION "b2-0.1.0"

// MCU GPIO map (circuit.json "gpio" table, B.2)
#define PIN_BOOT_N          0   // strapping, external 10k pull-up
#define PIN_TIMER_ARM       4   // MC14541B MR release + Q200 gate; active high; 10k pull-down
#define PIN_OUT_OE_N        6   // 74HC595 OE, active low; external 10k pull-up
#define PIN_OUT_LATCH       7   // 74HC595 RCLK; external 100k pull-down
#define PIN_USB_VBUS_SENSE  33  // input, informational only
#define PIN_SPI_SCK         39  // SPI_SCK_RAW -> 47R -> SPI_SCK (shared: W5500 + 3x74HC595)
#define PIN_SPI_MOSI        40  // SPI_MOSI_RAW -> 47R -> SPI_MOSI (shared)
#define PIN_SPI_MISO        41  // from W5500 only
#define PIN_ETH_CS_N        42
#define PIN_ETH_RST_N       47
#define PIN_ETH_INT_N       48

// 74HC595 chain: MOSI -> U4 (DRV_01..08) -> U5 (DRV_09..16) -> U6 (DRV_17..20 on QA..QD).
// Shift order on the wire is U6 byte, U5 byte, U4 byte, MSB first; within a device bit0 = QA.
#define SR_DEVICES          3
#define DRV_COUNT           20

// Host h (1..10): POWER = DRV_(2h-1), RESET = DRV_(2h)  (host sheets R39/R43 ... R111/R115)
#define HOST_COUNT          10
#define DRV_POWER(host)     (2u * (host) - 1u)
#define DRV_RESET(host)     (2u * (host))

// Timing limits. The MC14541B window (200k/1nF C0G, 32768 counts) is about 15.07 s and cuts the
// rail regardless of firmware; firmware never requests more than PRESS_MAX_MS.
#define PRESS_MIN_MS        100
#define PRESS_MAX_MS        10000
#define ARM_LOW_GAP_MS      50      // datasheet note on the outputs sheet: ARM low >= 10 ms between commands
#define RAIL_SETTLE_MS      5       // Q4 turn-on + TLP3122A tON (2 ms typ, 3 ms max) is inside the press time

// SPI
#define SPI_HOST_USED       SPI2_HOST
#define ETH_SPI_CLOCK_HZ    (8 * 1000 * 1000)   // HARDWARE.md: start at 8 MHz and verify timing
#define SR_SPI_CLOCK_HZ     (2 * 1000 * 1000)
